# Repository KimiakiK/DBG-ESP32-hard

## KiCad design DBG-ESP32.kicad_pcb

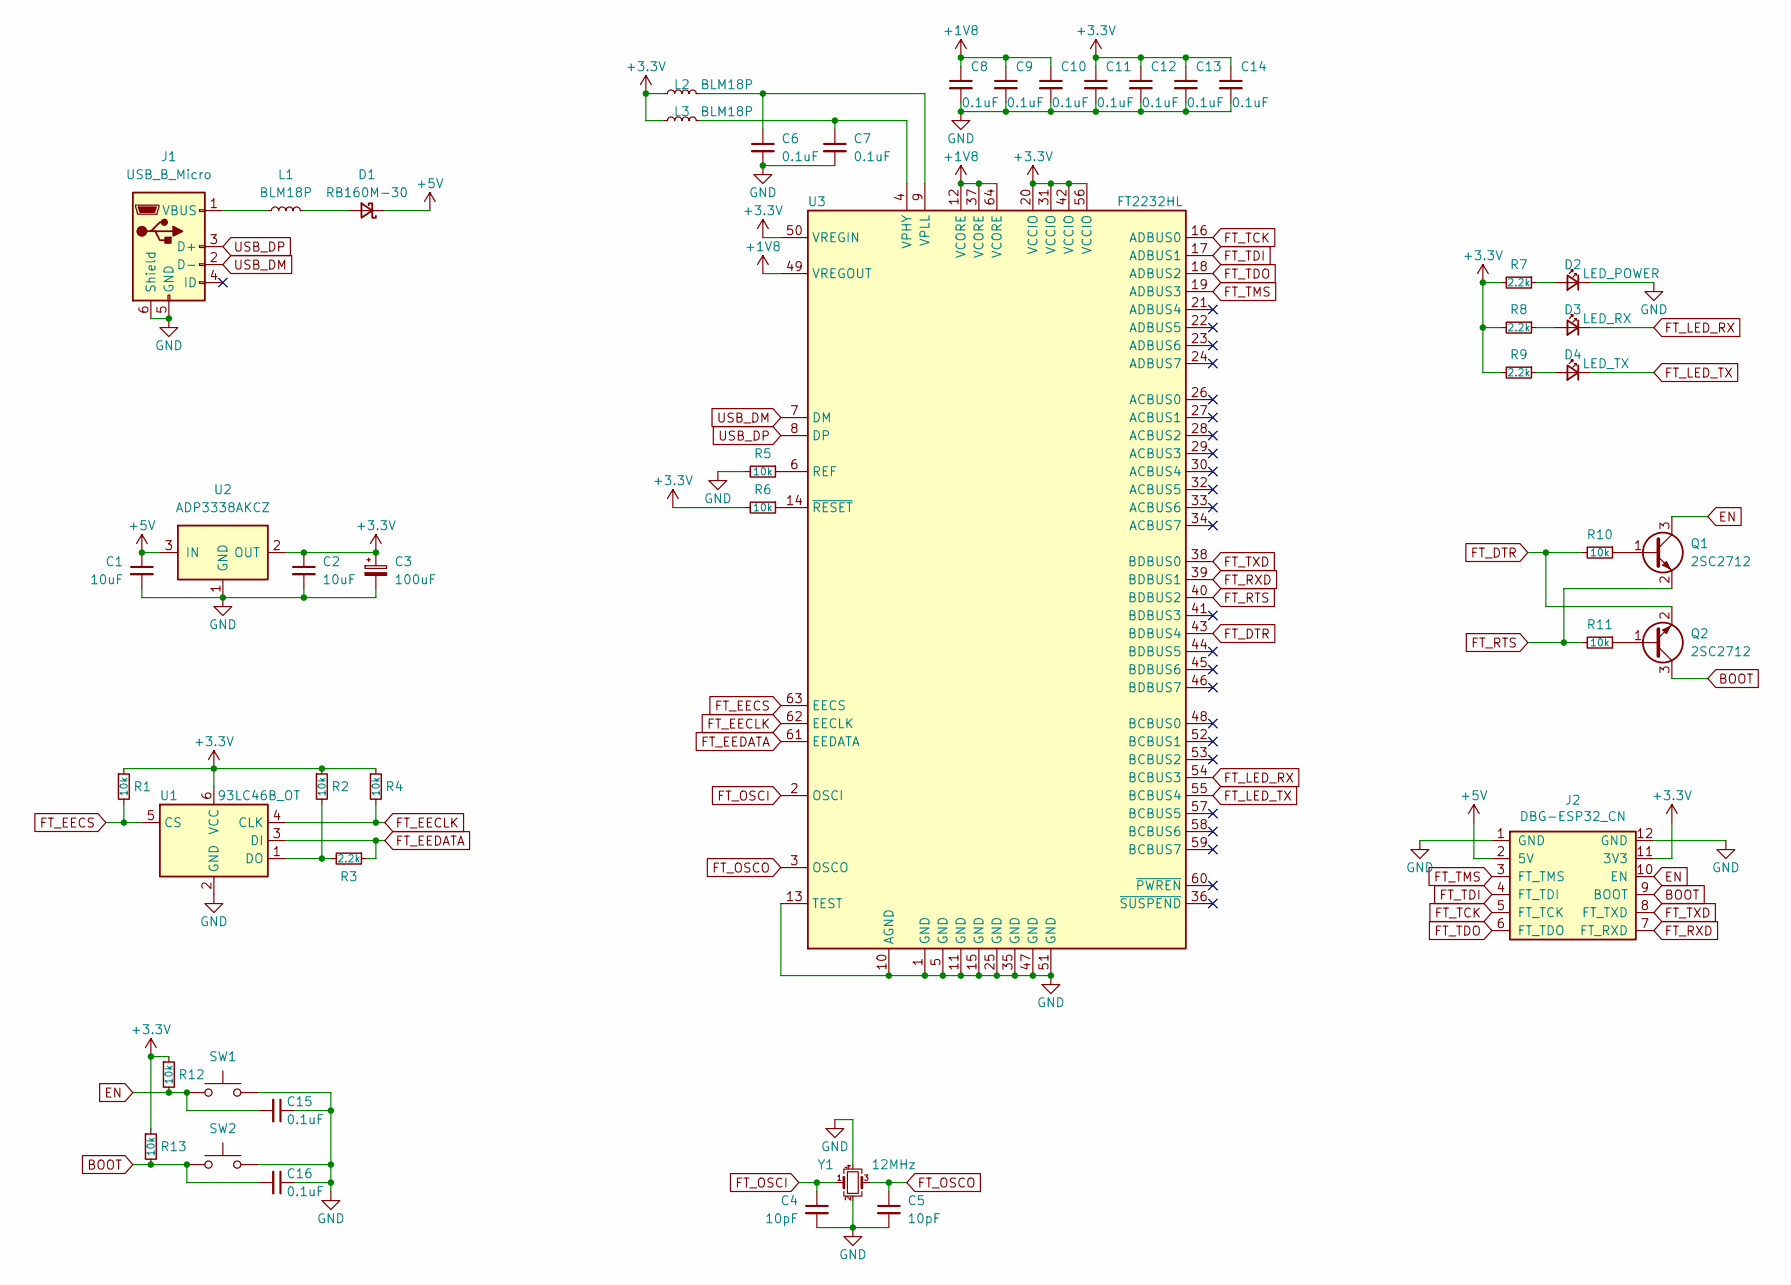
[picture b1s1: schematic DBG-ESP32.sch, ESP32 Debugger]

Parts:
C1, C2: 10uF; 1608Metric
C3: 100uF; CP_Elec_6.3x7.7
C4, C5: 10pF; 1005Metric
C6, C7, C8, C9, C10, C11, C12, C13, C14, C15, C16: 0.1uF; 1608Metric
D1: RB160M-30; D_SOD-123
D2: LED_POWER; 1608Metric
D3: LED_RX; 1608Metric
D4: LED_TX; 1608Metric
J1: USB_B_Micro; ZX62-B-5PA_2
J2: DBG-ESP32_CN; DBG-ESP32-CN
L1, L2, L3: BLM18P; 1608Metric
Q1, Q2: 2SC2712; SOT-23
R1, R2, R4, R5, R6, R10, R11, R12, R13: 10k; 1608Metric
R3, R7, R8, R9: 2.2k; 1608Metric
SW1, SW2: SW_Push; SW_TVAF06
U1: 93LC46B_OT; SOT-23-6
U2: ADP3338AKCZ; SOT-223-3_TabPin2
U3: FT2232HL; LQFP-64-10x10mm-P0.5mm_FusionPCB
Y1: 12MHz; Crystal_SMD_3225-4Pin_3.2x2.5mm_HandSoldering

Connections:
+1V8: C8.1, C9.1, C10.1, U3.12 (VCORE), U3.37 (VCORE), U3.49 (VREGOUT), U3.64 (VCORE)
+3V3: C2.1, C3.1, C11.1, C12.1, C13.1, C14.1, J2.11 (3V3), L2.1, L3.1, R1.1, R2.1, R4.1, R6.2, R7.2, R8.2, R9.2, R12.1, R13.1, U1.6 (VCC), U2.2 (OUT), U3.20 (VCCIO), U3.31 (VCCIO), U3.42 (VCCIO), U3.50 (VREGIN), U3.56 (VCCIO)
+5V: C1.1, D1.1 (K), J2.2 (5V), U2.3 (IN)
BOOT: C16.2, J2.9 (BOOT), Q2.3 (C), R13.2, SW2.1
EN: C15.2, J2.10 (EN), Q1.3 (C), R12.2, SW1.1
FT_DTR: Q2.2 (E), R10.2, U3.43 (BDBUS4)
FT_EECLK: R4.2, U1.4 (CLK), U3.62 (EECLK)
FT_EECS: R1.2, U1.5 (CS), U3.63 (EECS)
FT_EEDATA: R3.1, U1.3 (DI), U3.61 (EEDATA)
FT_LED_RX: D3.1 (K), U3.54 (BCBUS3)
FT_LED_TX: D4.1 (K), U3.55 (BCBUS4)
FT_OSCI: C4.1, U3.2 (OSCI), Y1.1
FT_OSCO: C5.1, U3.3 (OSCO), Y1.3
FT_RTS: Q1.2 (E), R11.2, U3.40 (BDBUS2)
FT_RXD: J2.7 (FT_RXD), U3.39 (BDBUS1)
FT_TCK: J2.5 (FT_TCK), U3.16 (ADBUS0)
FT_TDI: J2.4 (FT_TDI), U3.17 (ADBUS1)
FT_TDO: J2.6 (FT_TDO), U3.18 (ADBUS2)
FT_TMS: J2.3 (FT_TMS), U3.19 (ADBUS3)
FT_TXD: J2.8 (FT_TXD), U3.38 (BDBUS0)
GND: C1.2, C2.2, C3.2, C4.2, C5.2, C6.2, C7.2, C8.2, C9.2, C10.2, C11.2, C12.2, C13.2, C14.2, C15.1, C16.1, D2.1 (K), J1.5 (GND), J1.6 (Shield), J2.1 (GND), J2.12 (GND), R5.2, SW1.2, SW2.2, U1.2 (GND), U2.1 (GND), U3.1 (GND), U3.5 (GND), U3.10 (AGND), U3.11 (GND), U3.13 (TEST), U3.15 (GND), U3.25 (GND), U3.35 (GND), U3.47 (GND), U3.51 (GND), Y1.2, Y1.4
unnamed: C6.1, L2.2, U3.9 (VPLL)
unnamed: C7.1, L3.2, U3.4 (VPHY)
unnamed: D1.2 (A), L1.2
unnamed: D2.2 (A), R7.1
unnamed: D3.2 (A), R8.1
unnamed: D4.2 (A), R9.1
unnamed: J1.1 (VBUS), L1.1
unnamed: Q1.1 (B), R10.1
unnamed: Q2.1 (B), R11.1
unnamed: R2.2, R3.2, U1.1 (DO)
unnamed: R5.1, U3.6 (REF)
unnamed: R6.1, U3.14 (~RESET)
USB_DM: J1.2 (D-), U3.7 (DM)
USB_DP: J1.3 (D+), U3.8 (DP)

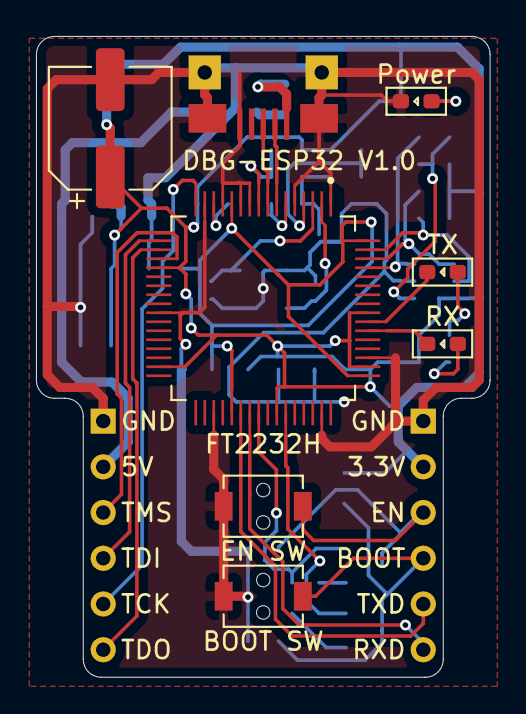
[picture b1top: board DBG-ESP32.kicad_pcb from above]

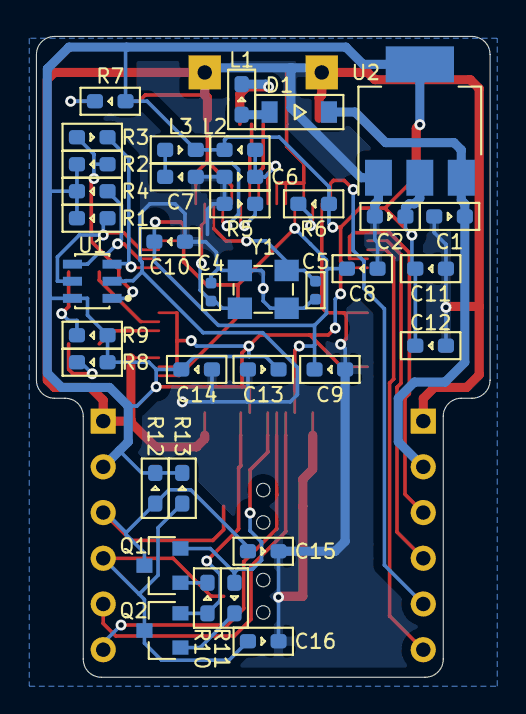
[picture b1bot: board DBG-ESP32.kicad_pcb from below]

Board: 2 copper layers, 25.2 x 35.6 mm, 46 parts (37 on the bottom side), 35 nets.

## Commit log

2021-12-01 基板 V1.0
